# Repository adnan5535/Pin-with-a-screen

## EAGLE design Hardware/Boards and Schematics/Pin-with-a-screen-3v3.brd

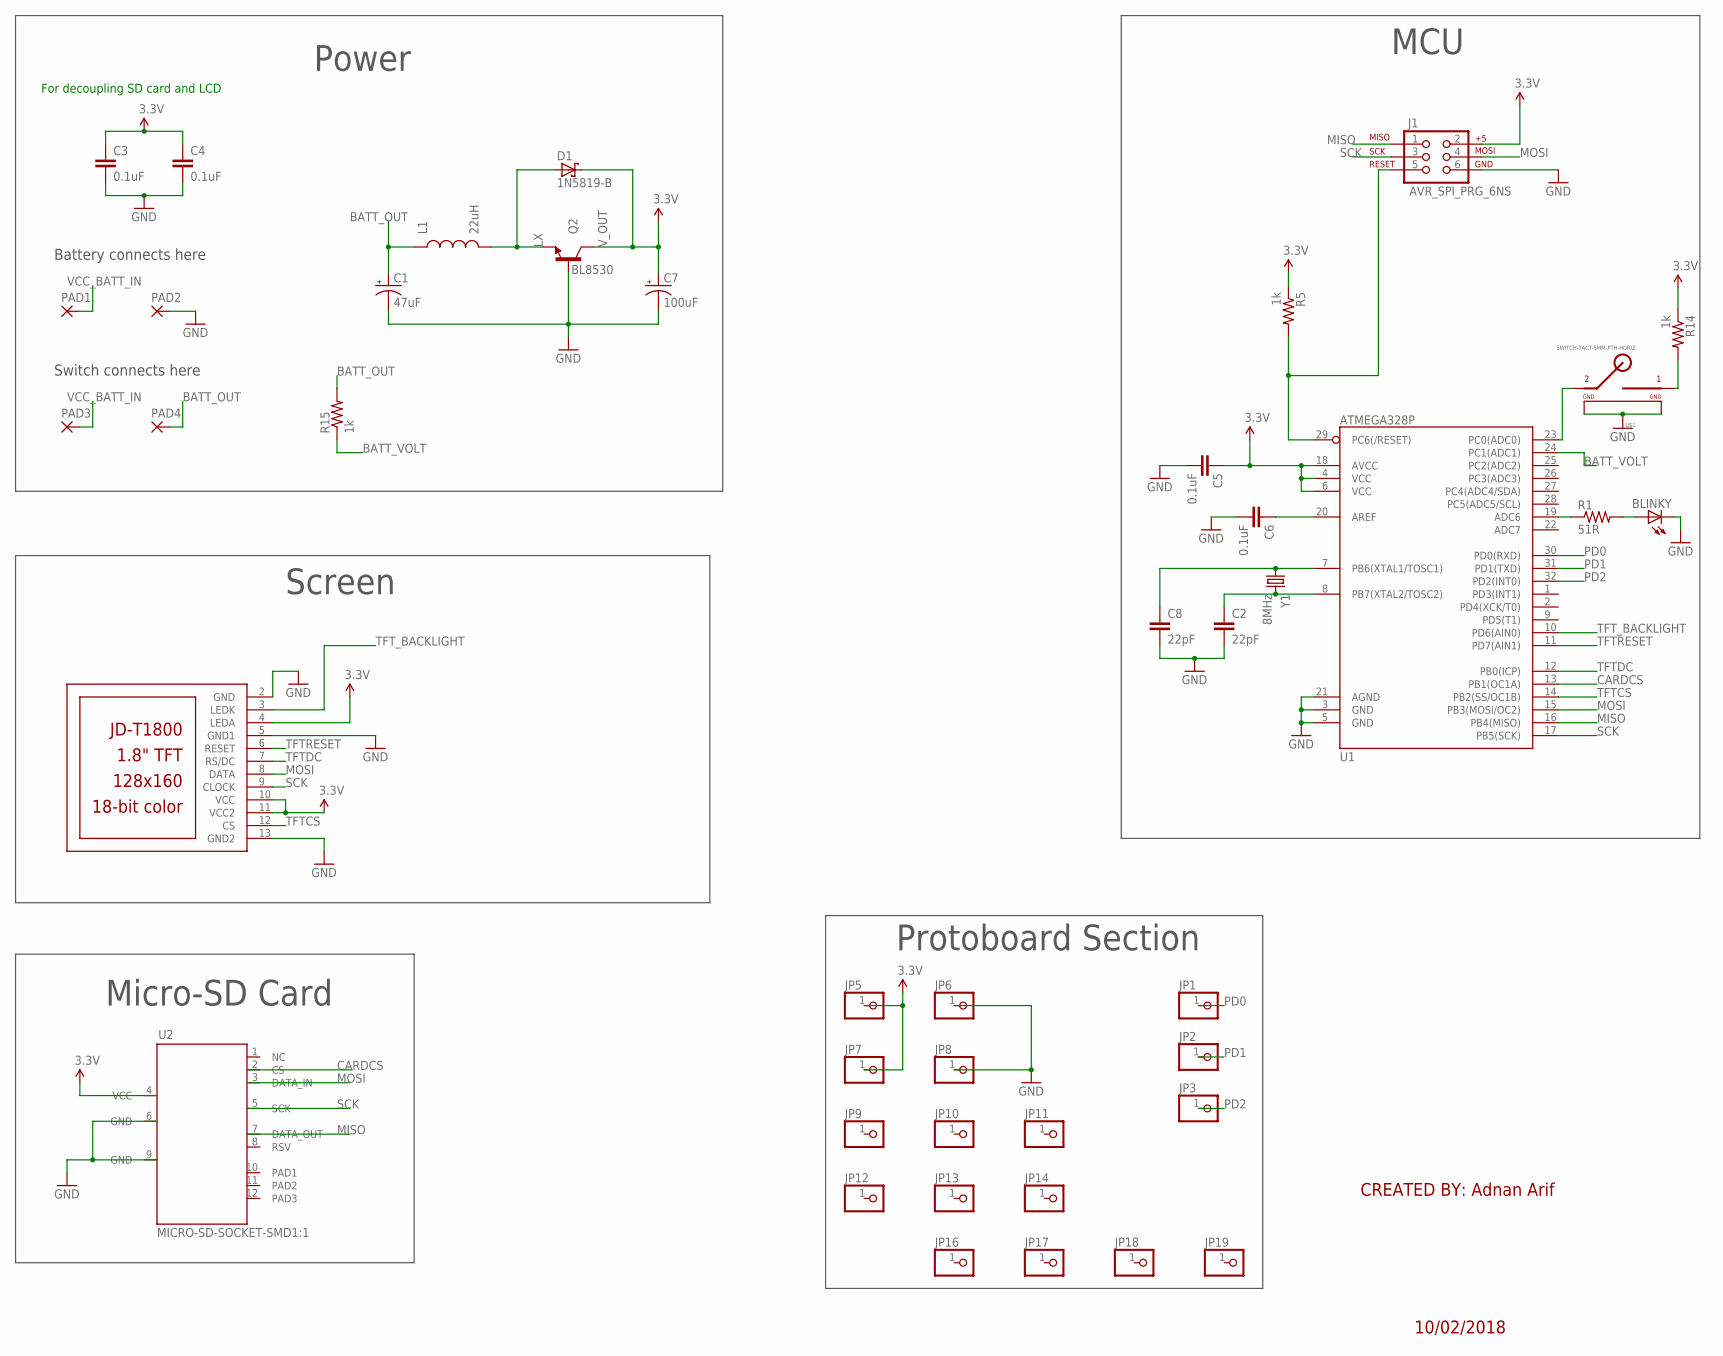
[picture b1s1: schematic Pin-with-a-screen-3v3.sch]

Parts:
BLINKY: Red; LED-0603
C1: 47uF; EIA3528-KIT
C2, C8: 22pF; 0603-CAP
C3, C4, C5, C6: 0.1uF; 0603-CAP
C7: 100uF; EIA3528-KIT
D1: 1N5819-B; DO41-7.6
J1: AVR_SPI_PRG_6NS; 2X3-NS
JP1, JP2, JP3, JP5, JP6, JP7, JP8, JP9, JP10, JP11, JP12, JP13, JP14, JP16, JP17, JP18, JP19: PINHD-1X1; 1X01
L1: 22uH; 0603
LCD2: JD-T1800
PAD1, PAD2, PAD3, PAD4: 2,15/1,0
Q2: BL8530; SOT89
R1: 51R; 0603-RES
R5, R14, R15: 1k; 0603-RES
U1: ATMEGA328P; TQFP32-08
U2: MICRO-SD-SOCKET-SMD1:1; MICRO-SD-SOCKET-SMD-1:1
U$1: SWITCH-TACT-5MM-PTH-HORIZ; 5MM-PTH
Y1: 8MHz; HC49UP

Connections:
3.3V: C3.1, C4.1, C5.1, C7.A (+), D1.C, J1.2, JP5.1, JP7.1, LCD2.4 (LEDA), LCD2.10 (VCC), LCD2.11 (VCC2), Q2.2 (C), R5.1, R14.1, U1.4 (VCC), U1.6 (VCC), U1.18 (AVCC), U2.4 (VCC)
BATT_OUT: C1.A (+), L1.1, PAD4.1, R15.2
BATT_VOLT: R15.1, U1.24 (PC1(ADC1))
CARDCS: U1.13 (PB1(OC1A)), U2.2 (CS)
GND: BLINKY.C, C1.C (-), C2.2, C3.2, C4.2, C5.2, C6.2, C7.C (-), C8.2, J1.6, JP6.1, JP8.1, LCD2.2 (GND), LCD2.5 (GND1), LCD2.13 (GND2), PAD2.1, Q2.1 (B), U1.3 (GND), U1.5 (GND), U1.21 (AGND), U2.6 (GND), U2.9 (GND), U$1.GND, U$1.GND1
LX: D1.A, L1.2, Q2.3 (E)
MISO: J1.1, U1.16 (PB4(MISO)), U2.7 (DATA_OUT)
MOSI: J1.4, LCD2.8 (DATA), U1.15 (PB3(MOSI/OC2)), U2.3 (DATA_IN)
unnamed: U1.23 (PC0(ADC0)), U$1.2
unnamed: R14.2, U$1.1
unnamed: C6.1, U1.20 (AREF)
unnamed: C8.1, U1.7 (PB6(XTAL1/TOSC1)), Y1.1
unnamed: C2.1, U1.8 (PB7(XTAL2/TOSC2)), Y1.2
unnamed: J1.5, R5.2, U1.29 (PC6(/RESET))
unnamed: R1.1, U1.19 (ADC6)
unnamed: BLINKY.A, R1.2
PD0: JP1.1, U1.30 (PD0(RXD))
PD1: JP2.1, U1.31 (PD1(TXD))
PD2: JP3.1, U1.32 (PD2(INT0))
SCK: J1.3, LCD2.9 (CLOCK), U1.17 (PB5(SCK)), U2.5 (SCK)
TFTCS: LCD2.12 (CS), U1.14 (PB2(SS/OC1B))
TFTDC: LCD2.7 (RS/DC), U1.12 (PB0(ICP))
TFTRESET: LCD2.6 (RESET), U1.11 (PD7(AIN1))
TFT_BACKLIGHT: LCD2.3 (LEDK), U1.10 (PD6(AIN0))
VCC_BATT_IN: PAD1.1, PAD3.1

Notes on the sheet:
For decoupling SD card and LCD
10/02/2018
Screen
Power
MCU
Micro-SD Card
CREATED BY: Adnan Arif
V_OUT
Battery connects here
Switch connects here
Protoboard Section

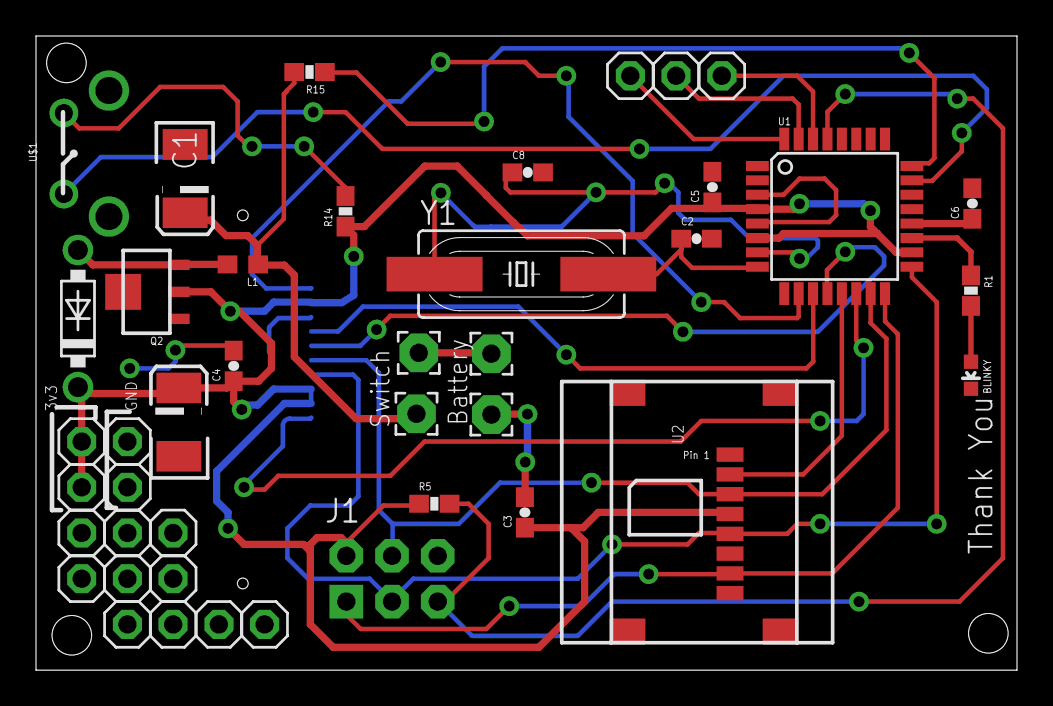
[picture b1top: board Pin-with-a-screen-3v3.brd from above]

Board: 2 copper layers, 54.5 x 35.2 mm, 43 parts (1 on the bottom side), 25 nets.

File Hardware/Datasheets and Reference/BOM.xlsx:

| Qty | Value | Device | Package | Parts | Description | PROD_ID | VALUE.1 | Column1
 | 4 | 0.1uF | CAP0603-CAP | 0603-CAP | C3, C4, C5, C6 | Capacitor
 | 1 | 100uF | CAP_POL3528-KIT | EIA3528-KIT | C7 | Capacitor Polarized
 | 2 | 22pF | CAP0603-CAP | 0603-CAP | C2, C8 | Capacitor
 | 1 | 47uF | CAP_POL3528-KIT | EIA3528-KIT | C1 | Capacitor Polarized
 | 4 | 1k | RESISTOR0603-RES | 0603-RES | R3, R5, R14, R15 | Resistor
 | 1 | 22R | RESISTOR0603-RES | 0603-RES | R4 | Resistor
 | 1 | 5R | RESISTOR0603-RES | 0603-RES | R1 | Resistor
 | 1 | 22uH | INDUCTOR0603 | 0603 | L1 | Inductors
 | 1 | 1N5819-B | Diode1N5819-B | DO41-7.6 | D1 | 1.0A SCHOTTKY BARRIER RECTIFIER
 | 1 | BL8530 | 3.3V Regulator - SOT89 | SOT89 | Q2 | Transistor NPN
 | 1 | MMBT2222A | TRANSISTOR_NPNMMBT2222A | SOT23-3 | Q1 | Generic NPN BJT | TRANS-08049 | MMBT2222A
 | 1 | 8MHz | CRYSTALSMD | HC49UP | Y1 | Various standard crystals. Proven footprints. Spark Fun Electronics SKU : COM-0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
 | 1 | ATMEGA328P | ATMEGA328_SMT | TQFP32-08 | U1 | 32-Pin Atmega328 part | IC-09069 | ATMEGA328P
 | 1 | AVR_SPI_PRG_6NS | AVR_SPI_PRG_6NS | 2X3-NS | J1 | AVR ISP 6 Pin
 | 1 | Button McButtonface | TAC_SWITCHPTH | TACTILE-PTH | S1 | Momentary Switch
 | 1 | Green | LED0603 | LED-0603 | BLINKY | LEDs
 | 1 | JD-T1800 | JD-T1800 | JD-T1800 | LCD2
 | 2 | M02POGO_PIN_HOLES_ONLY | M02POGO_PIN_HOLES_ONLY | 1X02_PP_HOLES_ONLY | 9V_BATT, POWSWITCH | Standard 2-pin 0.1 header. Use with"
 | 1 | MICRO-SD-SOCKET-SMD1:1 | MICRO-SD-SOCKET-SMD1:1 | MICRO-SD-SOCKET-SMD-1:1 | U2 | This footprint was created for a Transflash TF micro SD card socket purchased f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
 | 1 | 2x AA Battery holder
 | 1 | switch
 |  | solder wick
 |  | soldering iron
 |  | soldering paste/flux

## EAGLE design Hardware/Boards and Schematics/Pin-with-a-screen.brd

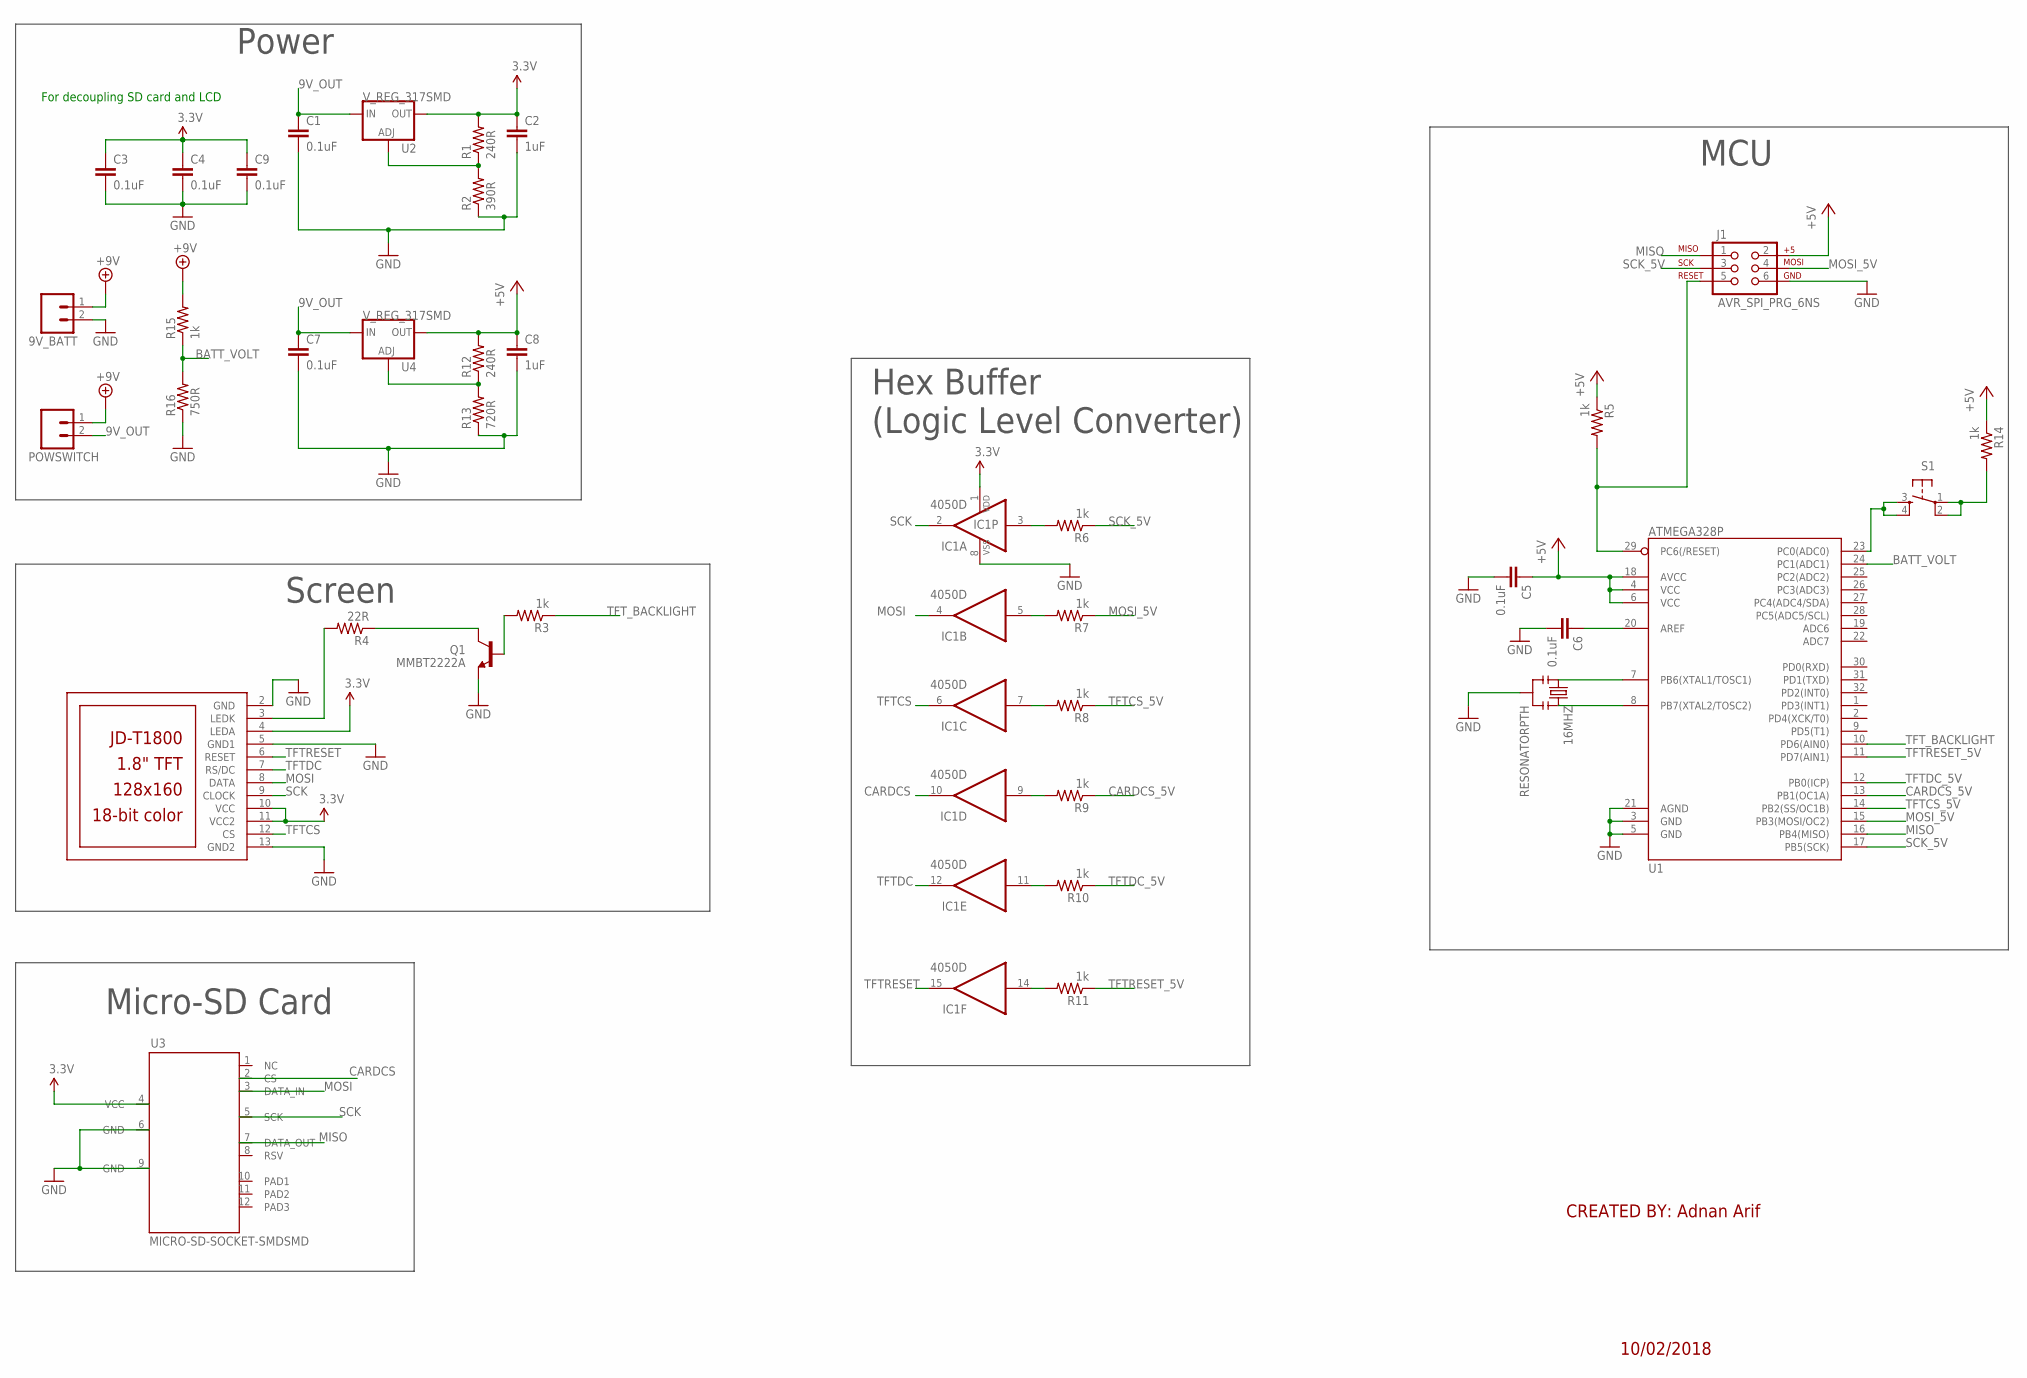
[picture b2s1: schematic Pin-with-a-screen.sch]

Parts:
9V_BATT: M02POGO_PIN_HOLES_ONLY; 1X02_PP_HOLES_ONLY
16MHZ: RESONATORPTH; RESONATOR-PTH
C1, C3, C4, C5, C6, C7, C9: 0.1uF; 0603-CAP
C2, C8: 1uF; 0603-CAP
IC1: 4050D; SO16
J1: AVR_SPI_PRG_6NS; 2X3-NS
LCD2: JD-T1800
POWSWITCH: M02POGO_PIN_HOLES_ONLY; 1X02_PP_HOLES_ONLY
Q1: MMBT2222A; SOT23-3
R1, R12: 240R; 0603-RES
R2: 390R; 0603-RES
R3, R5, R6, R7, R8, R9, R10, R11, R14, R15: 1k; 0603-RES
R4: 22R; 0603-RES
R13: 720R; 0603-RES
R16: 750R; 0603-RES
S1: TAC_SWITCHPTH; TACTILE-PTH
U1: ATMEGA328P; TQFP32-08
U2, U4: V_REG_317SMD; SOT223
U3: MICRO-SD-SOCKET-SMDSMD; MICRO-SD-SOCKET-SMD

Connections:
3.3V: C2.1, C3.1, C4.1, C9.1, IC1.1 (VDD), LCD2.4 (LEDA), LCD2.10 (VCC), LCD2.11 (VCC2), R1.2, U2.2 (OUT), U3.4 (VCC)
9V_OUT: C1.1, C7.1, POWSWITCH.2, U2.3 (IN), U4.3 (IN)
+5V: C5.1, C8.1, J1.2, R5.1, R12.2, R14.1, U1.4 (VCC), U1.6 (VCC), U1.18 (AVCC), U4.2 (OUT)
+9V: 9V_BATT.1, POWSWITCH.1, R15.2
BATT_VOLT: R15.1, R16.2, U1.24 (PC1(ADC1))
CARDCS: IC1.10 (O), U3.2 (CS)
CARDCS_5V: R9.1, U1.13 (PB1(OC1A))
GND: 9V_BATT.2, 16MHZ.2, C1.2, C2.2, C3.2, C4.2, C5.2, C6.2, C7.2, C8.2, C9.2, IC1.8 (VSS), J1.6, LCD2.2 (GND), LCD2.5 (GND1), LCD2.13 (GND2), Q1.2 (E), R2.1, R13.1, R16.1, U1.3 (GND), U1.5 (GND), U1.21 (AGND), U3.6 (GND), U3.9 (GND)
LEDK: LCD2.3 (LEDK), R4.2
MISO: J1.1, U1.16 (PB4(MISO)), U3.7 (DATA_OUT)
MOSI: IC1.4 (O), LCD2.8 (DATA), U3.3 (DATA_IN)
MOSI_5V: J1.4, R7.1, U1.15 (PB3(MOSI/OC2))
unnamed: S1.3, S1.4, U1.23 (PC0(ADC0))
unnamed: R14.2, S1.1, S1.2
unnamed: C6.1, U1.20 (AREF)
unnamed: 16MHZ.1, U1.7 (PB6(XTAL1/TOSC1))
unnamed: 16MHZ.3, U1.8 (PB7(XTAL2/TOSC2))
unnamed: J1.5, R5.2, U1.29 (PC6(/RESET))
unnamed: IC1.3 (I), R6.2
unnamed: IC1.5 (I), R7.2
unnamed: IC1.7 (I), R8.2
unnamed: IC1.9 (I), R9.2
unnamed: IC1.11 (I), R10.2
unnamed: IC1.14 (I), R11.2
unnamed: R1.1, R2.2, U2.1 (ADJ)
unnamed: R12.1, R13.2, U4.1 (ADJ)
SCK: IC1.2 (O), LCD2.9 (CLOCK), U3.5 (SCK)
SCK_5V: J1.3, R6.1, U1.17 (PB5(SCK))
TFTCS: IC1.6 (O), LCD2.12 (CS)
TFTCS_5V: R8.1, U1.14 (PB2(SS/OC1B))
TFTDC: IC1.12 (O), LCD2.7 (RS/DC)
TFTDC_5V: R10.1, U1.12 (PB0(ICP))
TFTRESET: IC1.15 (O), LCD2.6 (RESET)
TFTRESET_5V: R11.1, U1.11 (PD7(AIN1))
TFT_BACKLIGHT: R3.1, U1.10 (PD6(AIN0))
TRAN_BASE: Q1.1 (B), R3.2
TRAN_COLLECTOR: Q1.3 (C), R4.1

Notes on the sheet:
For decoupling SD card and LCD
10/02/2018
Screen
Power
MCU
Micro-SD Card
Hex Buffer (Logic Level Converter)
CREATED BY: Adnan Arif

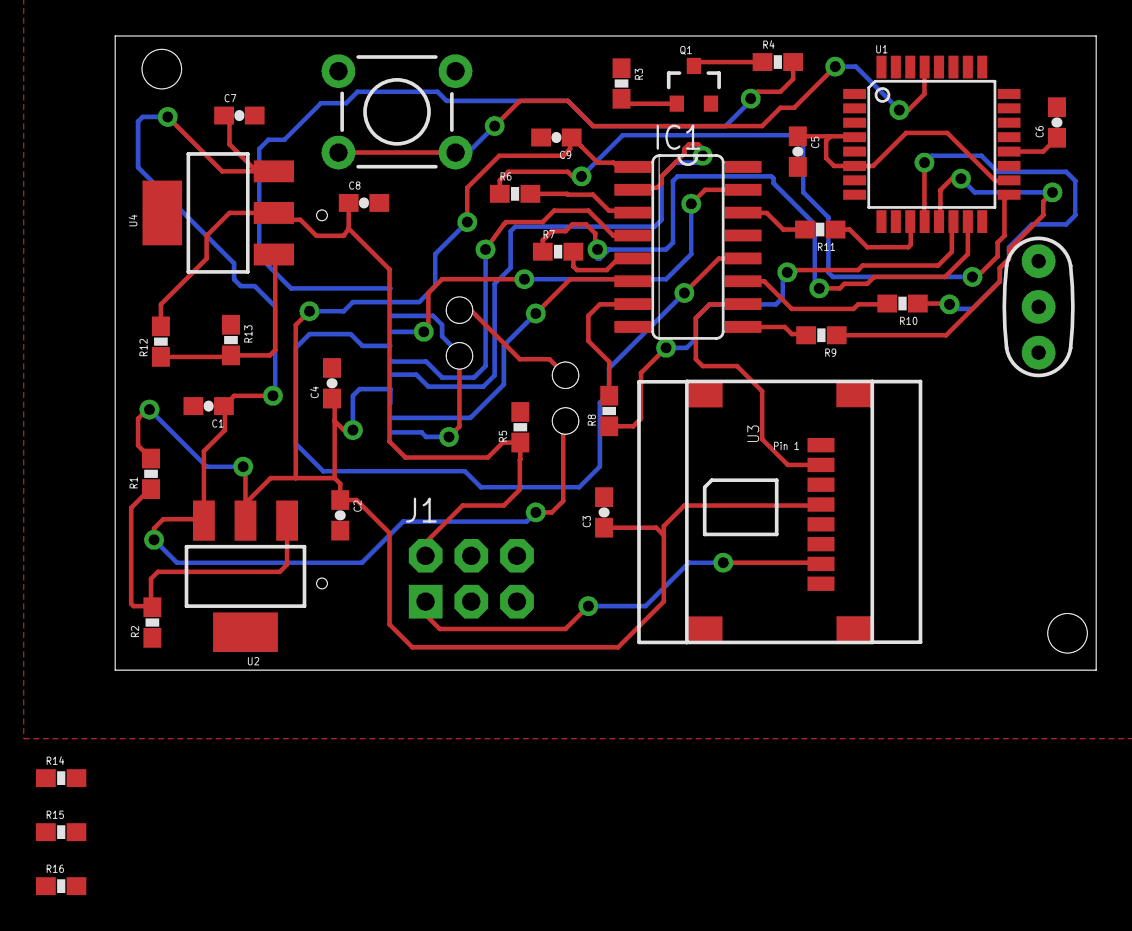
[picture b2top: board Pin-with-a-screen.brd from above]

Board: 2 copper layers, 54.5 x 35.2 mm, 37 parts (1 on the bottom side), 37 nets.

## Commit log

2018-04-08 Removed transistor-resistor logic level shifter
    Logic level shifter was used for PWM-ing backlight signal for screen.
    Since MCU operates on 3v3 logic like screen, level shifter is not
    necessary.
2018-04-08 Changed led to red and series resistor to 51R
2018-04-09 Added protoboard section
2018-04-14 Added "thank you", protoboard labels, gerbers
    Added thank you message to tnames layer
    Added labels for 3v3 and GND sections of protoboard
    Generated gerbers using SEEED studio and Sparkfun CAM files. Added .zip
    files for both
2018-04-15 Changed button to horizontal type, added screw-hole
    Push button changed to horizontal with custom footprint. It replaced the
    vertical push button. Some traces were re-routed to accomodate it.
    Screw-hole added to bottom left of board since top left one could have
    issues with push button.
2018-04-15 Generated gerbers using Seeed studio CAM file
2018-04-15 Changed switch configuration, generated gerbers
    Switch now connects directly to bottom side of PCB instead of being
    wired to pads. Horizontal SPDT switch selected.
    New gerbers generated with Seeed Studio CAM file.
2018-04-15 Changed horizontal button position
    Moved horizontal button inwards so that it doesn't stick out so much.
2018-04-15 Generated gerbers
    Generated new gerbers with Seeed studio CAM job file. Also deleted
    autosave files.

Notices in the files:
parts and their libraries:
SparkFun: Licensing: CC v3.0 Share-Alike You are welcome to use this library for commercial purposes.
